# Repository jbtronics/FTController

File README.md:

# FTController

Der FTController ist eine Motorsteuerung hauptsächlich entwickelt für Fischertechnik. Mittels zweier Joysticks lassen sich 4 analoge Motorausgänge, plus ein Digitalausgang steuern.

## Funktionen
* 4 (bipolare) Analoge Motorausgänge, verschiedene Übertragungsfunktionen auswählbar (digital, linear, quadratisch, logarithmisch, etc.)
* 1 (unipolarer) Digitaler Leistungsausgang (schaltbar über rechten Joysticktaster)
* 1 Impulszähleingang, für Frequenz oder Umdrehungszahlmessung (mit einstellbarem Multiplikator und Teilungsverhältnis)
* Eingangsspannung und Ausgangsstrommessung
* Virtuelle Einrastfunktion: Wird während der Bedienung der Joysticks der linke Joystick doppelt gedrückt, so wird der aktuelle Wert eingefroren (d.h. der Motorwert wird beibehalten auch wenn der Stick losgelassen wird)
* Ansteuermöglichkeit für Raupenketten (Vor/Rück, Links/Rechts-Bewegung an den Joysticks wird auf Raupenkettenantrieb umgesetzt)
* Möglichkeit zur Funkübertragung vorgesehen, d.h. zukünftig auch drahtlose Steuerung möglich.

## Technische Daten
* Eingangsspannungsbereich: 7 - 15 V; Empfohlen: 8 - 10V
* Strombelastbarkeit (Summe aller Ausgänge): max 1,5A
* Strombelastbarkeit *OUT*-Ausgang: max. 500mA
* ATMega328 als Steuerung, d.h. Firmware-Updates via ISP möglich
* Software Arduino kompatibel

## Lizenzen
Für Details siehe `LICENSE.md` in den entsprechenden Verzeichnissen.
* Software: Die Software steht unter der General Public License 3.0
* Hardware: Die Design-Files für die Hardware stehen unter "Creative Commons Attribution-NonCommercial 4.0 International (CC BY-NC 4.0)"

## Benötigte Bauteile
[Hier](https://hackaday.io/project/20349/components) kann eine Liste benötigter Bauteile gefunden werden. Keine Garantie auf Vollständigkeit, sicherer ist der Schaltplan oder die interaktive Bauteileliste die unter `hardware/bom` gefunden werden kann.

## Galerie:
### PCB:

### Fertiges Gerät:

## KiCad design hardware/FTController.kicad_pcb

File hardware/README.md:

# FTController - Hardware

In this folder you can find the KiCAD project for the FTController PCB.
Open FTController with KiCAD 5, and enjoy...

## Some interesting folders

* `bom`: An interactive HTML page which shows, which parts are needed for the PCB and where they are placed. (Generated using [this](https://github.com/openscopeproject/InteractiveHtmlBom))
* `export`: Here you can find some renderings of the PCB
* `gerber`: Here you can find the gerber files for the PCB.

## Changelog

* *Version 1.0*: Initial Version
* *Version 1.1*: Fixed the problem that the Basis pin were used on the CNY17 optocoupler instead of the collector.

## License
The hardware design files are licensed under "Creative Commons Attribution-NonCommercial 4.0 International (CC BY-NC 4.0)". See [here](https://creativecommons.org/licenses/by-nc/4.0/) for more infos.

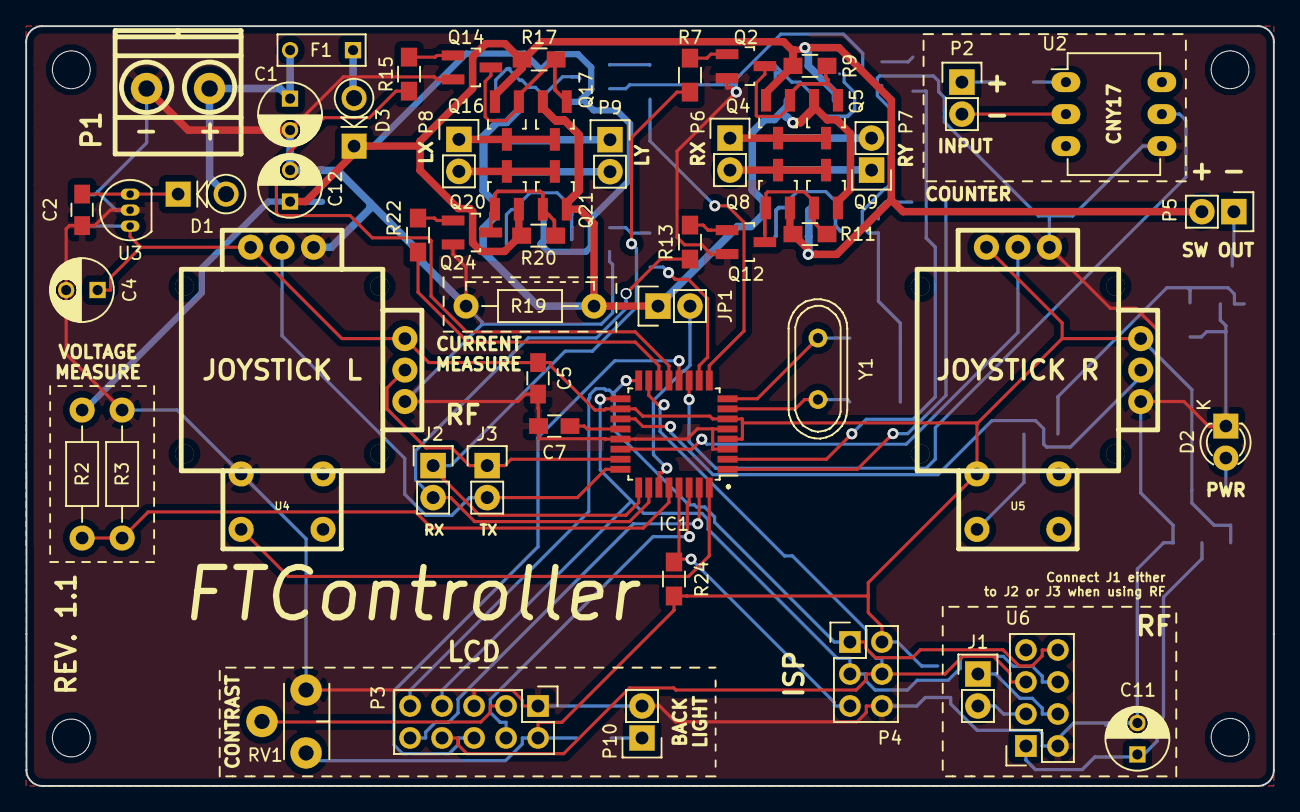
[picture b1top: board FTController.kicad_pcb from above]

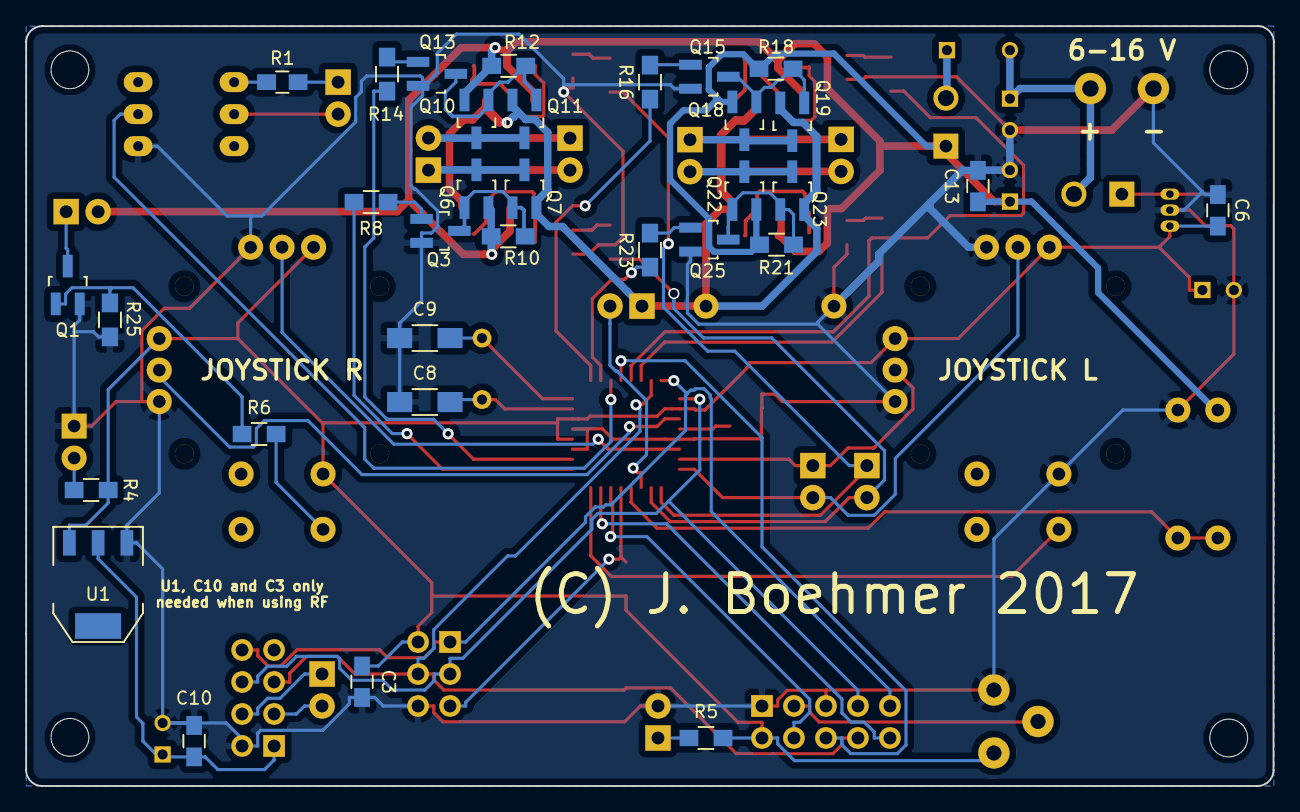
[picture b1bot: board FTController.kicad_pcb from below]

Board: 2 copper layers, 99.1 x 60.3 mm, 94 parts (33 on the bottom side), 69 nets.

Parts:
C1, C12: 100u; C_Radial_D5_L11_P2.5
C2, C3, C5, C6, C7, C10, C13: 100n; C_0805_HandSoldering
C4: 10uF; C_Radial_D5_L11_P2.5
C8, C9: 15p; C_1206_HandSoldering
C11: 10u; C_Radial_D5_L11_P2.5
D1: 1N4001; Diode_DO-41_SOD81_Vertical_KathodeUp
D2: PWR; LED-3MM
D3: SB560; Diode_DO-41_SOD81_Vertical_KathodeUp
F1: 1.5A; C_Rect_L7_W2.5_P5
IC1: ATMEGA328-AU; TQFP-32_7x7mm_Pitch0.8mm
J1: RF; Pin_Header_Straight_1x02
J2: RF_A; Pin_Header_Straight_1x02
J3: RF_B; Pin_Header_Straight_1x02
JP1: I_M_ON; Pin_Header_Straight_1x02
MK1, MK2, MK3, MK4: Mounting_Hole; MountingHole_3mm
P1: 9V IN; mkds_1,5-2
P2: COUNTER; Pin_Header_Straight_1x02
P3: LCD; Pin_Header_Straight_2x05
P4: AVR-ISP; Pin_Header_Straight_2x03
P5: SW_OUTPUT; Pin_Header_Straight_1x02
P6: OUT_RX; Pin_Header_Straight_1x02
P7: OUT_RY; Pin_Header_Straight_1x02
P8: OUT_LX; Pin_Header_Straight_1x02
P9: OUT_LY; Pin_Header_Straight_1x02
P10: LCD_BACKLIGHT; Pin_Header_Straight_1x02
Q1, Q5, Q7, Q9, Q11, Q17, Q19, Q21, Q23: IRML2502; SOT-23_Handsoldering
Q2, Q3, Q12, Q13, Q14, Q15, Q24, Q25: BC848; SOT-23_Handsoldering
Q4, Q6, Q8, Q10, Q16, Q18, Q20, Q22: IRML6402; SOT-23_Handsoldering
R1: 1k; C_0805_HandSoldering
R2, R3: R; Resistor_Horizontal_RM10mm
R4, R5: 470; R_0805_HandSoldering
R6, R7, R8, R13, R14, R15, R16, R22, R23: 1k; R_0805_HandSoldering
R9, R10, R11, R12, R17, R18, R20, R21, R24, R25: 10k; R_0805_HandSoldering
R19: SHUNT; Resistor_Horizontal_RM10mm
RV1: CONTRAST; Potentiometer_VishaySpectrol-Econtrim-Type36X
U1: LD1117S33TR; SOT-223
U2: CNY17-1; DIP-6_W7.62mm_LongPads
U3: LM78L05ACZ; TO-92_Inline_Narrow_Oval
U4: JOYSTICK_L; Joystick_Button
U5: JOYSTICK_R; Joystick_Button
U6: NRF24L01; Socket_Strip_Straight_2x04
Y1: 16MHz; Crystal_HC49-U_Vertical

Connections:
+5V: C3.1, C4.1, C5.1, C6.1, IC1.4, IC1.6, IC1.18, P3.2, P4.2, R4.2, R5.2, R24.1, RV1.1, U1.3, U3.1, U4.X1, U4.Y1, U5.SW1, U5.X1, U5.Y1
+9V: C12.1, C13.1, D3.1, P5.2, Q4.2, Q6.2, Q8.2, Q10.2, Q16.2, Q18.2, Q20.2, Q22.2, R2.1, R9.1, R10.1, R11.1, R12.1, R17.1, R18.1, R20.1, R21.1
/COUNT: IC1.11, U2.5
/JOYL_X: IC1.23, J3.1, U4.X2
/JOYL_Y: IC1.24, J3.2, U4.Y2
/JOYR_X: IC1.19, U5.X2
/JOYR_Y: IC1.22, U5.Y2
/LCD_DB7: IC1.31, P3.10
/LCD_E: IC1.12, P3.6
/LCD_RS: IC1.30, P3.4
/MISO: IC1.16, P3.9, P4.1, U6.8
/MOSI: IC1.15, P3.8, P4.4, U6.5
/RST: IC1.29, P4.5, R24.2
/SCK: IC1.17, P3.7, P4.3, U6.6
/SCL: IC1.28, R2.2, R3.1
/SW_L: IC1.32, U4.SW2
/XTAL1: C8.2, IC1.7, Y1.2
/XTAL2: C9.2, IC1.8, Y1.1
GND: C1.2, C2.2, C3.2, C4.2, C5.2, C6.2, C7.2, C8.1, C9.1, C10.2, C11.2, C12.2, C13.2, D2.1, IC1.3, IC1.5, IC1.21, P1.2, P3.1, P3.5, P4.6, P10.2, Q1.2, Q2.2, Q3.2, Q12.2, Q13.2, Q14.2, Q15.2, Q24.2, Q25.2, R3.2, R19.2, R25.2, RV1.3, U1.1, U2.4, U3.2, U4.SW1, U4.X3, U4.Y3, U5.X3, U5.Y3, U6.2
GNDA: JP1.1, Q5.2, Q7.2, Q9.2, Q11.2, Q17.2, Q19.2, Q21.2, Q23.2, R19.1
I_MEAS: IC1.27, JP1.2
unnamed: C1.1, D1.2, F1.2, P1.1
unnamed: C2.1, D1.1, U3.3
unnamed: C7.1, IC1.20
unnamed: C10.1, C11.1, U1.2, U6.1
unnamed: D2.2, R4.1
unnamed: D3.2, F1.1
unnamed: J1.1, U6.4
unnamed: J1.2, U6.3
unnamed: P2.1, R1.2
unnamed: P2.2, U2.2
unnamed: P3.3, RV1.2
unnamed: P5.1, Q1.3
unnamed: P6.1, Q4.3, Q5.3
unnamed: P6.2, Q8.3, Q9.3
unnamed: P7.1, Q6.3, Q7.3
unnamed: P7.2, Q10.3, Q11.3
unnamed: P8.1, Q16.3, Q17.3
unnamed: P8.2, Q20.3, Q21.3
unnamed: P9.1, Q18.3, Q19.3
unnamed: P9.2, Q22.3, Q23.3
unnamed: P10.1, R5.1
unnamed: Q1.1, R6.1, R25.1
unnamed: Q2.1, R7.1
unnamed: Q2.3, Q4.1, Q5.1, R9.2
unnamed: Q3.1, R8.1
unnamed: Q3.3, Q6.1, Q7.1, R10.2
unnamed: Q10.1, Q11.1, Q13.3, R12.2
unnamed: Q12.1, R13.1
unnamed: Q8.1, Q9.1, Q12.3, R11.2
unnamed: Q13.1, R14.1
unnamed: Q14.1, R15.1
unnamed: Q14.3, Q16.1, Q17.1, R17.2
unnamed: Q15.1, R16.1
unnamed: Q15.3, Q18.1, Q19.1, R18.2
unnamed: Q20.1, Q21.1, Q24.3, R20.2
unnamed: Q22.1, Q23.1, Q25.3, R21.2
unnamed: Q24.1, R22.1
unnamed: Q25.1, R23.1
unnamed: R1.1, U2.1
PWM_LX1: IC1.13, R15.2
PWM_LX2: IC1.14, R22.2
PWM_LY1: IC1.9, R16.2
PWM_LY2: IC1.10, R23.2
PWM_RX1: IC1.25, J2.1, R7.2
PWM_RX2: IC1.26, J2.2, R13.2
PWM_RY1: IC1.1, R8.2
PWM_RY2: IC1.2, R14.2
SW_R: R6.2, U5.SW2

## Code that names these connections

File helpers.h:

// helpers_c.h

#ifndef _HELPERS_C_h
#define _HELPERS_C_h

#if defined(ARDUINO) && ARDUINO >= 100
	#include "arduino.h"
#else
	#include "WProgram.h"
#endif

#include "config.h"
#include "chars.h"

#include <SoftPWM.h>

/********************************
* Lookup Tables
*********************************/
//Square lookup (f(x)=51/125x^2)
const PROGMEM uint8_t TABLE_SQUARE[26] = {0, 0, 2, 4, 7,  10, 15, 20, 26, 33, 41, 49, 59, 69, 80, 92, 104, 118, 132, 147, 163, 180, 198, 216, 235, 255};
//Exponential lookup(f(x) = e^0.2216505418)
const PROGMEM uint8_t TABLE_EXP[26] = {0, 1, 1, 2, 2, 2, 3, 4, 6, 7, 9, 11, 14, 18, 22, 28, 35, 43, 54, 67, 84, 105, 131, 164, 204, 255};
//Logarithmic lookup(f(x) = 78.26655748 * ln(x+1)
const PROGMEM uint8_t TABLE_LOG[26] = { 0, 54, 86, 109, 126, 140, 152, 163, 172, 180, 188, 194, 201, 207, 212, 217, 222, 226, 230, 234, 238, 242, 245, 249, 252, 255 };
//Square root lookup(f(x) = 51 * SQRT(x))
const PROGMEM uint8_t TABLE_SQRT[26] = { 0, 51, 72, 88, 102, 114, 125, 135, 144, 153, 161, 169, 177, 184, 191, 198, 204, 210, 216, 222, 228, 233, 239, 245, 250, 255 };

/*********************************
*	Pin Defines
**********************************/

//PWM Outputs
#define PWM_LX1		9	//PB1
#define PWM_LX2		10	//PB2
#define PWM_LY1		5	//PD5
#define PWM_LY2		6	//PD6
#define PWM_RX1		A2	//PC2
#define PWM_RX2		A3	//PC3
#define PWM_RY1		3	//PD3
#define PWM_RY2		4	//PD4

//Joystick inputs
#define PIN_JOYL_X		A0
#define PIN_JOYL_Y		A1
#define PIN_JOYR_X		A6
#define PIN_JOYR_Y		A7
#define SW_L		2	//Joystick button on PD2

//Counter
#define PIN_COUNT		7	//PD

//LCD
#define LCD_RS		0	//PD0
#ifdef DISPLAY_FIX
#define LCD_E		MEAS_VOLT
#else
#define LCD_E		8	//PB0
#endif
#define LCD_D4		13	//PB5
#define LCD_D5		11	//PB3
#define LCD_D6		12	//PB4
#define LCD_D7		1	//PD1

//Measurement
#define	MEAS_VOLT	A5
#define MEAS_CURR	A4

/**************************
* Helper defines
***************************/
//Motors
#define MOTOR_LX	0
#define MOTOR_LY	1
#define MOTOR_RX	2
#define MOTOR_RY	3

#define MOTOR_HALT	0
#define MOTOR_FWD	1
#define MOTOR_REV	2

#define MOTOR_LX1	PWM_LX1
#define MOTOR_LX2	PWM_LX2
#define MOTOR_LY1	PWM_LY1
#define MOTOR_LY2	PWM_LY2
#define MOTOR_RX1	PWM_RX1
#define MOTOR_RX2	PWM_RX2
#define MOTOR_RY1	PWM_RY1
#define MOTOR_RY2	PWM_RY2

//Joysticks
//X and Y axis has to be switched
#define JOYL_X		PIN_JOYL_Y
#define JOYL_Y		PIN_JOYL_X
#define JOYR_X		PIN_JOYR_Y
#define JOYR_Y		PIN_JOYR_X


#define JOYSTICK_LX		0
#define JOYSTICK_LY		1
#define JOYSTICK_RX		2
#define JOYSTICK_RY		3

/*************************
* Modes
*************************/
#define MODE_NOTHING	0	//Dont react to input of the joysticks
#define MODE_DIGITAL	1	
#define MODE_ANALOG		2
#define MODE_EXP		3
#define MODE_SQUARE		4
#define MODE_LN			5
#define MODE_SQRT		6

#define MODE_MAX_VAL	6	//Whats the index of the Mode with the highest value
#define MODE_DEFAULT	MODE_DIGITAL

//Display mode
#define DISPLAY_INPUT	0	//Shows the input values of the joysticks
#define DISPLAY_VOLT	1	//Shows the input and MCU voltage
#define DISPLAY_OUT		2	//Shows the output values
#define DISPLAY_RPM		3	//Shows RPM rate
#define DISPLAY_COUNT	4
#define DISPLAY_TEMP	5	//Shows temperature

#define DISPLAY_MAX_VAL	5
#define DISPLAY_DEFAULT	DISPLAY_VOLT

//Config Menu states
#define CONFIG_SPLASH	1
#define CONFIG_HALT		2
#define CONFIG_CUNIT	3
#define CONFIG_CDEBOUNCE 4
#define CONFIG_CMULTI	5
#define CONFIG_CDIVIDE	6
#define CONFIG_VERSION1	7
#define CONFIG_CREDIT	8

#define CONFIG_MAX_VAL	8
#define CONFIG_DEFAULT	CONFIG_SPLASH

//Menu states
#define MENU_HIDDEN		0
#define MENU_SHOW		1
#define MENU_MODES		1
#define MENU_DISPLAY	2
#define MENU_CONFIG		3

#define MENU_MAX_VAL	3
#define MENU_DEFAULT	MENU_MODES

#define THRESHOLD_TIME	50

/************************
* EEPROM Adress defines
************************/
#define EEPROM_MODE		0x00
#define EEPROM_DISPLAY	0x01
#define EEPROM_HALT		0x02
#define EEPROM_CUNIT	0x03
#define EEPROM_CDEB		0x04
#define EEPROM_CMULTI	0x05
#define EEPROM_CDIVIDE	0x06

/***********************
* FAILSAFE STATES
***********************/
#define FAILSAFE_OFF		0
#define FAILSAFE_HALT		1
#define FAILSAFE_CURRENT	2

/************************
* Counter units
*************************/
#define CUNIT_HZ			0
#define CUNIT_RPM			1


/*************************
* Makros
*************************** */
#define motor_output_analog_table(motor, value, table) motor_output_analog_no_thre(motor, map_joy_with_table(value, table));
#define TOGGLE_SETTING(x) x==0 ? x=1 : x=0


/*************************
* Functions declarations
**************************/
void init_all();
void init_motors();
void init_counter();
void motor_output_digtal(uint8_t motor, uint8_t mode);
void motor_output_analog(uint8_t motor, int16_t value);
void motor_output_analog_raw(uint8_t motor, int16_t value);
uint16_t read_MCU_volt();	//Gets the voltage of the AVR (should be around 5V)
uint16_t read_input_volt();	//Gets the voltage of the input
int16_t map_joy_with_table(int16_t val, const uint8_t[25]); //Map the value using the given lookup table
void stop_motors();	//Halt all motors
void pcint_handler();
unsigned long counter_val();
void counter_reset();
double GetTemp(void);

/************************
* Structs
************************/
struct config_struct {
	uint8_t emergency_halt  : 1;
	uint8_t counter_unit : 1;
	uint8_t counter_debounce : 1;
	uint8_t counter_multi;
	uint8_t counter_divide;
};


#endif

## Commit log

2017-04-03 GITIGNORE und GITATTRIBUTES hinzufügen.
2017-04-03 Projektdateien hinzufügen.
2017-04-03 Added modes with exponential, logarithmic, square and square root.
2017-04-03 Jump to the first mode, when the last one was reached and vice versa.
2017-04-03 Freeze the input value, when double click the menu button.
2017-04-03 Added submenu for changing the Display Mode.
2017-07-29 Added a temperature view menu. Prepared some functions for counter.
2017-07-30 Moved menu functions to menu.cpp. Added a config menu and a emergency halt function.
2017-07-30 Save emergency halt setting in EEPROM.
2017-07-30 Failsafe message does not flicker any more.
2017-07-31 Added a counter function. Allow to switch between Hz and RPM display.
2017-07-31 added possibility to debounce the input. Save debounce and counter unit setting in EEPROM.
2017-07-31 Allow usage of both x and y axis on right stick for toggeling settings.
2017-07-31 Added multiplier and divider for counter.
2017-07-31 Added counter mode, where the count get increment whenever a falling edge on input is present. Reset with double click.
2017-08-03 Added Current measurement.
2017-08-03 Use two digits for Voltage in display_power
2018-08-14 Moved software into its own folder.
2018-08-14 Added KiCAD files to project.
2018-08-15 Added german manual.
2018-08-15 Updated KiCAD files for KiCAD 5.0 and exported schematics
2018-08-15 Updated gerber files
2018-08-15 Added interactive BOM for PCB.
2018-08-15 Added readme to the hardware files.
2018-08-15 Added README to the software section.
2018-08-15 Moved arduino sketch into a FTController folder, so it can be opened with the arduino IDE easily.
2018-08-15 Added compiled hex file.
2018-08-15 Licensed the software under GPL 3.0
2018-08-15 Added license hint for the hardware files.
2018-08-15 Added README.md for the main project.
2018-08-15 Added pictures.
2018-08-15 Added an gallery section to README...
2018-11-30 [ImgBot] Optimize images
    *Total -- 2,841.97kb -> 2,709.82kb (4.65%)
    /hardware/export/renderings/PCB/bottom.png -- 74.68kb -> 54.75kb (26.69%)
    /hardware/export/renderings/PCB/top.png -- 80.06kb -> 60.28kb (24.71%)
    /documentation/pictures/pic3.jpg -- 138.64kb -> 131.81kb (4.93%)
    /hardware/export/renderings/with_parts/1.png -- 439.91kb -> 421.80kb (4.12%)
    /documentation/pictures/pic4.jpg -- 155.88kb -> 150.01kb (3.76%)
